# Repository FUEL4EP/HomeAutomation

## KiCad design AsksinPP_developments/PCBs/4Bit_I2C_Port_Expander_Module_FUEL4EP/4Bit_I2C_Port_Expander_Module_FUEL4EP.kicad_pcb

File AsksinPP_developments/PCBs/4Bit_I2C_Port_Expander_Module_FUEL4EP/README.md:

# 4Bit_I2C_Port_Expander_Module_FUEL4EP  

## I2C 4 Port Expander Aufsteckplatine für DIY AsksinPP-Projekte

- basierend auf [PCA9536](https://www.mouser.de/datasheet/2/302/PCA9536-3139488.pdf)

- passend zu
	* [HB-UNI-SEN-BATT_ATMega1284P_E07-868MS10_FUEL4EP](https://github.com/FUEL4EP/HomeAutomation/tree/master/AsksinPP_developments/PCBs/HB-UNI-SEN-BATT_ATMega1284P_E07-868MS10_FUEL4EP)
	* [HB-UNI-SEN-BATT_ATMega1284P_E07-868MS10_FRAM_FUEL4EP](https://github.com/FUEL4EP/HomeAutomation/tree/master/AsksinPP_developments/PCBs/HB-UNI-SEN-BATT_ATMega1284P_E07-868MS10_FRAM_FUEL4EP)
	* [HB-UNI-SEN-BATT_FUEL4EP](https://github.com/FUEL4EP/HomeAutomation/tree/master/AsksinPP_developments/PCBs/HB-UNI-SEN-BATT_FUEL4EP)
	* [HB-UNI-SEN-BATT_ATMega1284P_E07-868MS10_FUEL4EP](https://github.com/FUEL4EP/HomeAutomation/tree/master/AsksinPP_developments/PCBs/HB-UNI-SEN-BATT_ATMega1284P_E07-868MS10_FUEL4EP)
	* Befestigung mit 2 Stiftleisten J1 und J2
	
- 4 zusätzliche PCA9536-IO-Ports, die I2C-steuerbar sind
- 4 zusätzliche 2N7000-Open-Collector-Ausgänge mit Pull-Up Widerständen

- Infos zu AsksinPP sind [hier](https://asksinpp.de) und [hier](https://asksinpp.de/Grundlagen/01_hardware.html#verdrahtung) zu finden

## Platinenmaße

- Breite: 30,48 mm
- Weite: 17 mm
- Platinendicke 1,2 mm (bei der Bestellung bei JLCPCB auswählen)

## Stromlaufplan

- ist [hier](./Schematics/4Bit_I2C_Port_Expander_Module_FUEL4EP.pdf)

## Status

- diese Platine wurde in der Version 1.1 bei JLCPCB gefertigt und ist erfolgreich validiert.
- zum Test wurde der Sketch PCA9536/examples/PCA9536_Test.ino verwendet.

## Rückmeldungen

- und Verbesserungsvorschläge sind willkommen.

## Daten für die Bestellung bei JLCPCB

- die Daten für die Bestellung liegen im Verzeichnis [./jlcpcb/production_files/](./jlcpcb/production_files/)
- Gerber-Daten als Zip-Datei
- BOM- und CPL-Daten als CSV-Datei

## lokale Installation des Github Releases auf Deinem Computer

- gehe bitte in Dein Zielinstallationsverzeichnis, wo Du mit der 4Bit_I2C_Port_Expander_Module_FUEL4EP Platine mit KiCAD arbeiten möchtest

  - gebe dort 'git clone https://github.com/FUEL4EP/HomeAutomation.git' ein
	  + damit lädst Du mein [Sammelrepository](https://github.com/FUEL4EP/HomeAutomation) für alle meine auf Github freigegebenen HomeBrew Entwicklungen herunter.
  - dann findest Du ein neues Verzeichnis 'HomeAutomation' auf Deinem Rechner, das alle meine auf Github freigebenen Entwicklungen enthält, siehe [README.md](https://github.com/FUEL4EP/HomeAutomation/blob/master/README.md)
  	+ mache bitte regelmäßig ein Update mit 'git pull'
 -	die Platine 4Bit_I2C_Port_Expander_Module_FUEL4EP findest Du unter './HomeAutomation/tree/master/AsksinPP_developments/PCBs/4Bit_I2C_Port_Expander_Module_FUEL4EP'
 
- alternativ kann vom Github [Sammelrepository](https://github.com/FUEL4EP/HomeAutomation) die ZIP-Datei HomeAutomation-master.zip heruntergeladen und auf dem lokalen Rechner ausgepackt werden. Bitte dann regelmäßig auf Github nach Updates schauen.

## Versionsverlauf

-   V1.0 03. Sep 2023: Initiale Veröffentlichung auf Github
-	V1.1 16. Dez 2023: Wechsel von 2N7000 auf 2N2007K wegen SMD Gehäuse
-	V1.2 29. Sep 2024: Migration auf KiCAD8
- KiCad Schaltplan-Editor Version: 8.0.5-8.0.5-0~ubuntu22.04.1, release build
 unter Kubuntu22.04.1
- KiCad Leiterplatteneditor Version: 8.0.5-8.0.5-0~ubuntu22.04.1, release build
 unter Kubuntu22.04.1
- PCB Version 1.2
- Schematics  1.2

## Disclaimer

-   die Nutzung der hier veröffentlichten Inhalte erfolgt vollständig auf eigenes Risiko und ohne jede Gewähr.

## Lizenz 

**Creative Commons BY-NC-SA**<br>
Give Credit, NonCommercial, ShareAlike

<br />This work is licensed under a <a rel="license" href="http://creativecommons.org/licenses/by-nc-sa/4.0/">Creative Commons Attribution-NonCommercial-ShareAlike 4.0 International License</a>.

-EOF

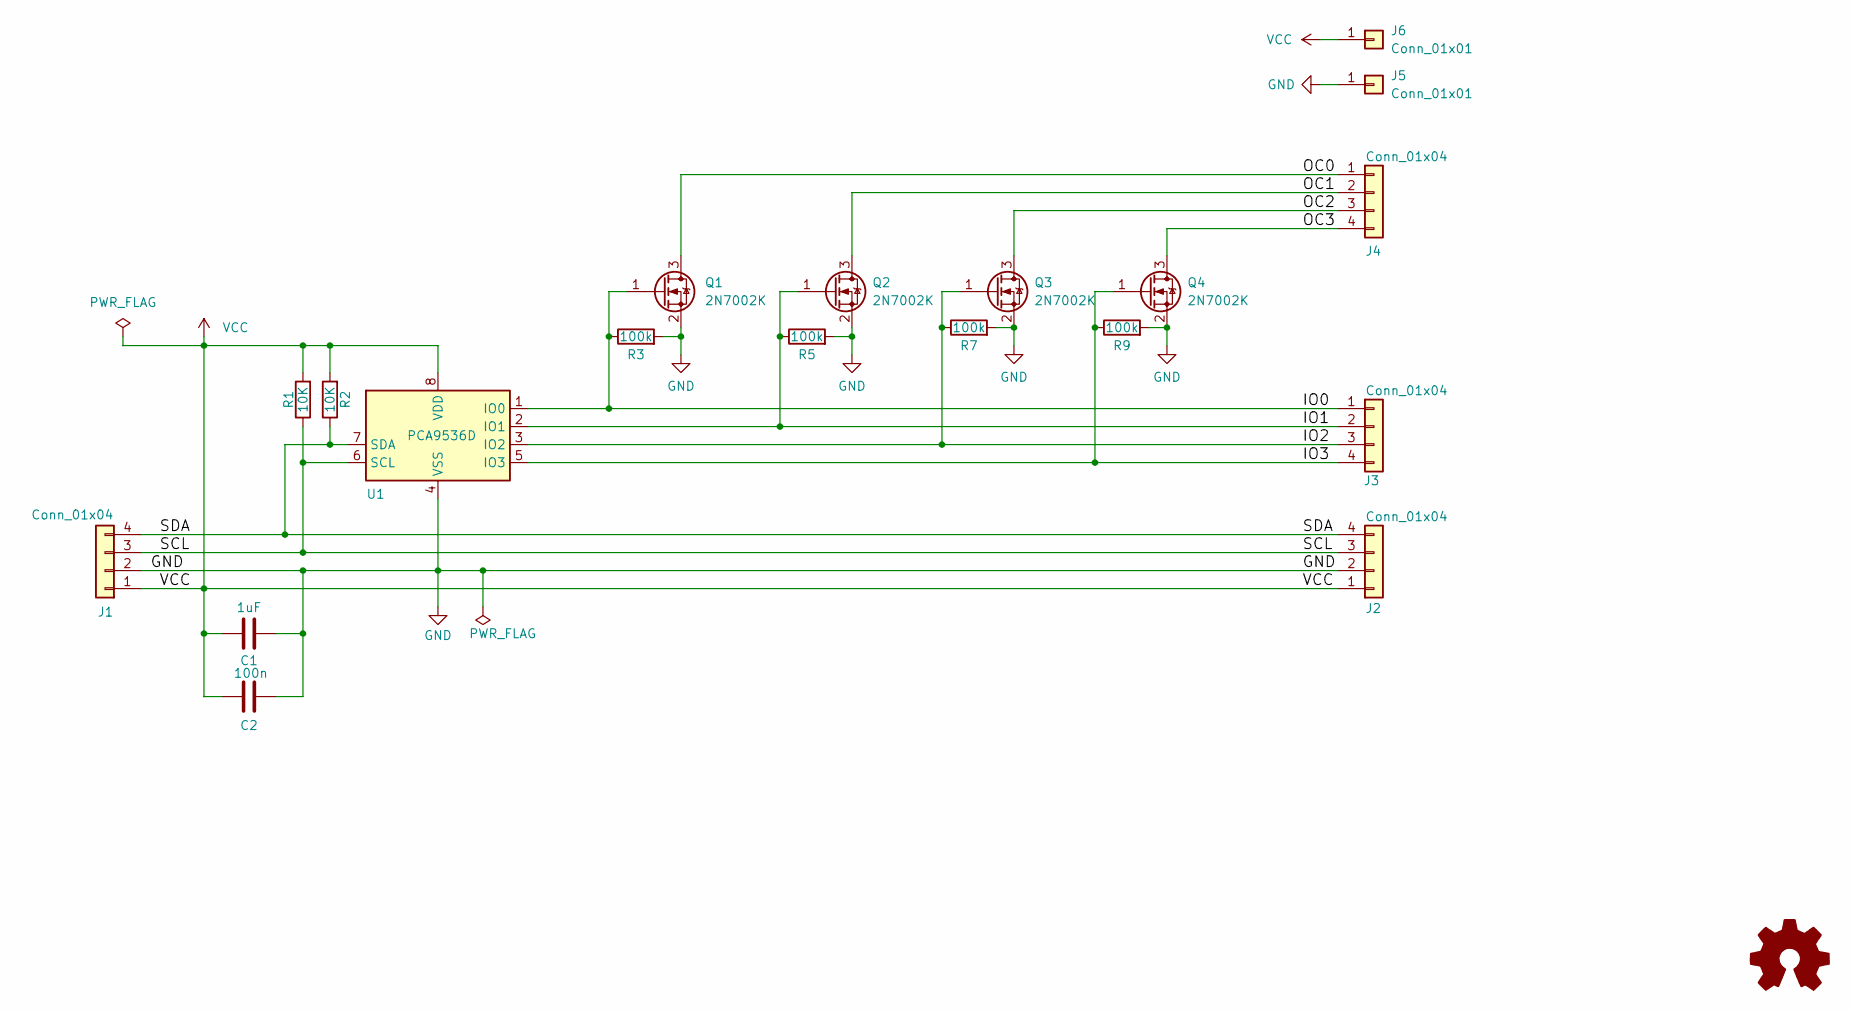
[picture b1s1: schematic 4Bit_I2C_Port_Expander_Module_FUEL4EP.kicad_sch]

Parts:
C1: 1uF; C_0603_1608Metric; LCSC C15849
C2: 100n; C_0402_1005Metric; LCSC C1525
J1, J2, J3, J4: Conn_01x04; PinHeader_1x04_P2.54mm_Vertical
J5, J6: Conn_01x01; TestPoint_THTPad_D1.0mm_Drill0.5mm
LOGO1: Logo_Open_Hardware_Small; CC-BY-ND-SA
Q1, Q2, Q3, Q4: 2N7002K; SOT-23; LCSC C114458
R1, R2: 10K; R_0402_1005Metric; LCSC C25744
R3, R5, R7, R9: 100k; R_0402_1005Metric; LCSC C25741
U1: PCA9536D; SOIC-8_3.9x4.9mm_P1.27mm; LCSC C129522

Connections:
/IO0: J3.1, Q1.1 (G), R3.1, U1.1 (IO0)
/IO1: J3.2, Q2.1 (G), R5.1, U1.2 (IO1)
/IO2: J3.3, Q3.1 (G), R7.1, U1.3 (IO2)
/IO3: J3.4, Q4.1 (G), R9.1, U1.5 (IO3)
/OC0: J4.1, Q1.3 (D)
/OC1: J4.2, Q2.3 (D)
/OC2: J4.3, Q3.3 (D)
/OC3: J4.4, Q4.3 (D)
/SCL: J1.3, J2.3, R1.1, U1.6 (SCL)
/SDA: J1.4, J2.4, R2.1, U1.7 (SDA)
GND: C1.2, C2.2, J1.2, J2.2, J5.1, Q1.2 (S), Q2.2 (S), Q3.2 (S), Q4.2 (S), R3.2, R5.2, R7.2, R9.2, U1.4 (VSS)
VCC: C1.1, C2.1, J1.1, J2.1, J6.1, R1.2, R2.2, U1.8 (VDD)

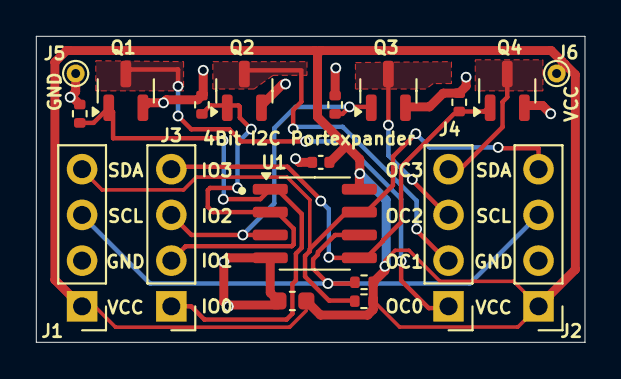
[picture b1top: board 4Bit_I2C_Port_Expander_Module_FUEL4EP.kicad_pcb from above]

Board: 2 copper layers, 30.5 x 17.0 mm, 20 parts (1 on the bottom side), 12 nets.

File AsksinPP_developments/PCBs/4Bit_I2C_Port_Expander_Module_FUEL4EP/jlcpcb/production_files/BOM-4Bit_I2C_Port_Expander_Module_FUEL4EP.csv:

Comment,Designator,Footprint,LCSC
2N7002K,"Q1,Q2,Q3,Q4",SOT-23,C114458
PCA9536D,U1,SOIC-8_3.9x4.9mm_P1.27mm,C129522
100n,C2,C_0402_1005Metric,C1525
1uF,C1,C_0603_1608Metric,C15849
100k,"R3,R5,R7,R9",R_0402_1005Metric,C25741
10K,"R1,R2",R_0402_1005Metric,C25744

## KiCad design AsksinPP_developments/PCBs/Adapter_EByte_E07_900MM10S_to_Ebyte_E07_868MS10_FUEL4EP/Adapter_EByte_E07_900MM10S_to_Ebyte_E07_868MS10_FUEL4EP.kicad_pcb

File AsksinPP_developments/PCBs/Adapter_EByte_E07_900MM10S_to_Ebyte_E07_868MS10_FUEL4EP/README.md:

# Adapter_EByte_E07_900MM10S_to_Ebyte_E07_868MS10_FUEL4EP  

## Ersatz für das eByte E07 868MS10 Modul 

- da das eByte E07 868MS10 Modul nicht mehr oder nur sehr schwer käuflich ist, wurde dieser Adapter als Ersatz entworfen. Es wird ein verfügbares EByte E07 900MM10S Funkmodul verbaut.

## Adapter für 868.3 MHz Funkmodul Ebyte E07 900MM10S auf Ebyte E07 868MS10

- Infos zu AsksinPP sind [hier](https://asksinpp.de) und [hier](https://asksinpp.de/Grundlagen/01_hardware.html#verdrahtung) zu finden

## Platinenmaße

- Breite: 19 mm
- Weite: 13 mm

## Stromlaufplan

- ist [hier](./Schematics/Adapter_EByte_E07_900MM10S_to_Ebyte_E07_868MS10_FUEL4EP.pdf)

## Status

- die Platine V1.1 wurde bei JLCPCB gefertigt und bestückt.
- der Frequenztest wurde am 25. Sep 2024 mit einem PCB HB-UNI-SEN-BATT_ATMega1284P_E07-868MS10_FUEL4EP erfolgreich durchgeführt.
- die Protokolldatei des Frequenztests ist [hier](./Log_files_as_reference/FreqTest_1284P_serial_monitor.log)
- Bilder der gefertigten Prototypen:

## Rückmeldungen

- sind willkommen.

## Daten für die Bestellung bei JLCPCB

- die Daten für die Bestellung liegen im Verzeichnis [./jlcpcb/production_files/](./jlcpcb/production_files/)
- Gerber-Daten als Zip-Datei
- BOM- und CPL-Daten als CSV-Datei

## Hinweis für Bestückung bei JLCPCB

- bei der Bestellung bitte angeben '[specify a location](https://jlcpcb.com/help/article/50-How-to-remove-order-number-from-your-PCB)'

- der  Dummy-Text 'JLCJLCJLCJLC' ist auf der Rückseite der Platine

- Bestückung des Funkmoduls Ebyte E07 900MM10S geht bei JLCPCB nur als teures Standard-PCBA. Handlöten ist eine günstigere Alternative.

## Hinweis für Bestückung von Hand

- die Ferritperle FB1 (0603) kann entweder mit
	+ Murata EMI Suppression Filter SMD0603 BLM18 470 Ohm, erhältlich z.B.  bei Reichelt als Bestellnummer [BLM18AG 471](https://www.reichelt.de/de/de/shop/produkt/emi_suppression_filter_smd0603_blm18_470_ohm-89677)
- oder bei geringeren Anforderungen an Störunterdrückung mit Lötzinn überbrückt werden

## Montage

- die Platine wird mit einer Stiftleiste RM 1.27mm 1x8 Pin auf die Basisplatine gelötet

## lokale Installation des Github Releases auf Deinem Computer

- gehe bitte in Dein Zielinstallationsverzeichnis, wo Du mit der Adapter_EByte_E07_900MM10S_to_Ebyte_E07_868MS10_FUEL4EP Platine mit KiCAD arbeiten möchtest

  - gebe dort 'git clone https://github.com/FUEL4EP/HomeAutomation.git' ein
	  + damit lädst Du mein [Sammelrepository](https://github.com/FUEL4EP/HomeAutomation) für alle meine auf Github freigegebenen HomeBrew Entwicklungen herunter.
  - dann findest Du ein neues Verzeichnis 'HomeAutomation' auf Deinem Rechner, das alle meine auf Github freigebenen Entwicklungen enthält, siehe [README.md](https://github.com/FUEL4EP/HomeAutomation/blob/master/README.md)
  	+ mache bitte regelmäßig ein Update mit 'git pull'
 -	die Platine Adapter_EByte_E07_900MM10S_to_Ebyte_E07_868MS10_FUEL4EP findest Du unter './HomeAutomation/tree/master/AsksinPP_developments/PCBs/Adapter_EByte_E07_900MM10S_to_Ebyte_E07_868MS10_FUEL4EP'
 
- alternativ kann vom Github [Sammelrepository](https://github.com/FUEL4EP/HomeAutomation) die ZIP-Datei HomeAutomation-master.zip heruntergeladen und auf dem lokalen Rechner ausgepackt werden. Bitte dann regelmäßig auf Github nach Updates schauen.

## Versionsverlauf

-   V1.0 24. Jun 2024: Initiale Version
-   V1.1 23. Sep 2024: Migration auf KiCAD 8; zusätzliche Vias
- KiCad Schaltplan-Editor Version: 8.0.5-8.0.5-0~ubuntu22.04.1 unter Kubuntu22.04.1
- KiCad Leiterplatteneditor Version: 8.0.5-8.0.5-0~ubuntu22.04.1 unter Kubuntu22.04.1
- PCB Version 1.1
- Schematics  1.1

## Disclaimer

-   die Nutzung der hier veröffentlichten Inhalte erfolgt vollständig auf eigenes Risiko und ohne jede Gewähr.
-  der Nutzer dieser Platine ist selbst dafür verantwortlich, dass die relevanten Richtlinien für Funkanlagen, z.B. in der EU die Funkanlagenrichtlinie (2014/53/EU, auch bekannt als RED), eingehalten wird.

## Lizenz 

**Creative Commons BY-NC-SA**<br>
Give Credit, NonCommercial, ShareAlike

<br />This work is licensed under a <a rel="license" href="http://creativecommons.org/licenses/by-nc-sa/4.0/">Creative Commons Attribution-NonCommercial-ShareAlike 4.0 International License</a>.

-EOF

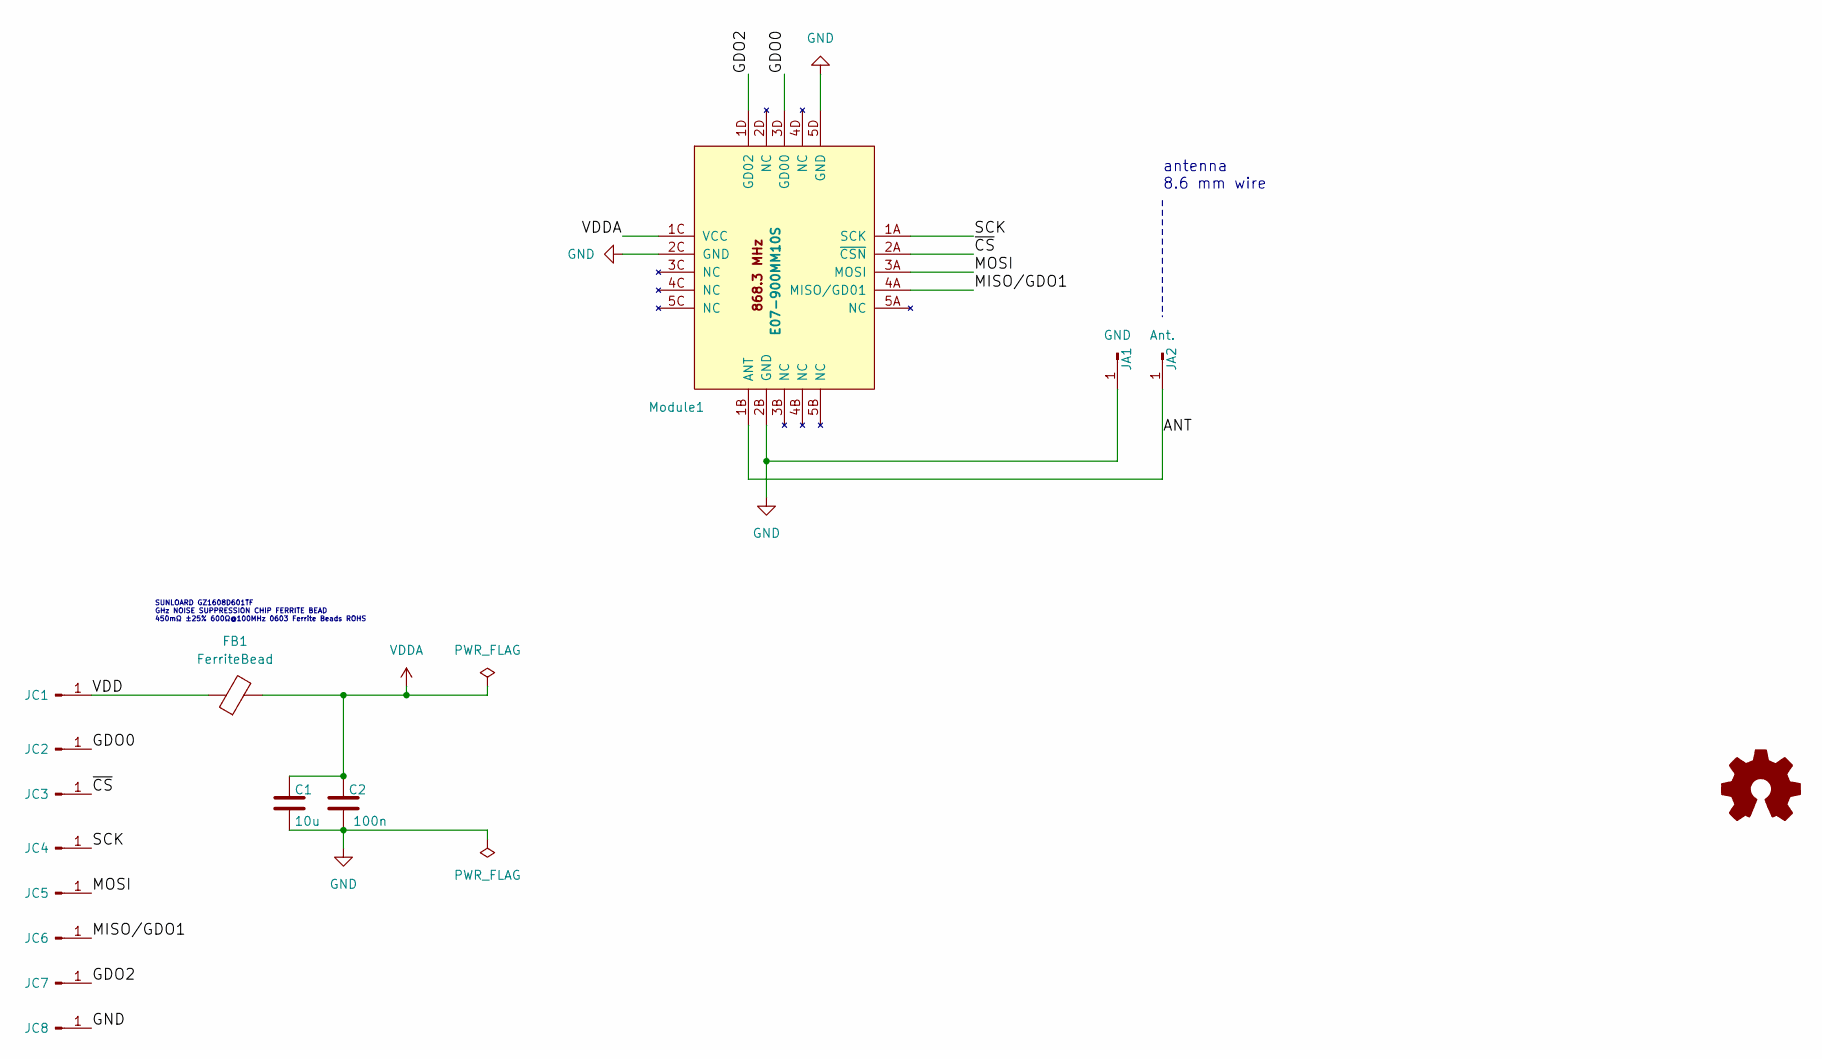
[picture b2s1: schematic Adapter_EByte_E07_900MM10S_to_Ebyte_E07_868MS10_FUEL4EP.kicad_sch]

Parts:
C1: 10u; C_0603_1608Metric; LCSC C19702
C2: 100n; C_0603_1608Metric; LCSC C14663
FB1: FerriteBead; L_0603_1608Metric; LCSC C1002
JA1: GND; edge_hole_Pitch2.28mm_Drill0.8mm
JA2: Ant.; edge_hole_Pitch2.28mm_Drill0.8mm
JC1: Conn_01x01_Pin; edge_hole_Pitch1.27mm_Drill0.75mm
JC2, JC3, JC4, JC5, JC6, JC7, JC8: Conn_01x01_Pin; edge_hole_Pitch1.27mm_Drill0.75mm_rounded
LOGO1: Logo_Open_Hardware_Small; CC-BY-ND-SA_bottom
Module1: E07-900MM10S; eByte_E07-900MM10S; LCSC C5844212

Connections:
/ANT: JA2.1, Module1.1B (ANT)
/GDO0: JC2.1, Module1.3D (GD00)
/GDO2: JC7.1, Module1.1D (GD02)
/MISO/GDO1: JC6.1, Module1.4A (MISO/GD01)
/MOSI: JC5.1, Module1.3A (MOSI)
/SCK: JC4.1, Module1.1A (SCK)
/VDD: FB1.1, JC1.1
/~CS: JC3.1, Module1.2A (~CSN)
GND: C1.2, C2.2, JA1.1, JC8.1, Module1.2B (GND), Module1.2C (GND), Module1.5D (GND)
VDDA: C1.1, C2.1, FB1.2, Module1.1C (VCC)

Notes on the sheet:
SUNLOARD GZ1608D601TF GHz NOISE SUPPRESSION CHIP FERRITE BEAD 450mΩ ±25% 600Ω@100MHz 0603 Ferrite Beads ROHS
antenna 8.6 mm wire

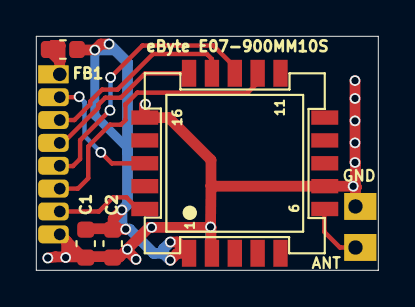
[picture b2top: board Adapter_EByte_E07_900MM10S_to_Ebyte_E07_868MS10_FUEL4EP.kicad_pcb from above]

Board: 2 copper layers, 19.0 x 13.0 mm, 15 parts (0 on the bottom side), 10 nets.

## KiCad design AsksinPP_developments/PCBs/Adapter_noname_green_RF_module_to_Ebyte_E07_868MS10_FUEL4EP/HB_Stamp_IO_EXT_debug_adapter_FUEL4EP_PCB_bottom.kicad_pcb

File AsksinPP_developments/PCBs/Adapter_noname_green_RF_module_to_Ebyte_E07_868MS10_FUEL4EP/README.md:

# Adapter_noname_green_RF_module_to_Ebyte_E07_868MS10_FUEL4EP  

## Ersatz für NoName grüne 868,3 MHz Modul

- da das NoName grüne 868,3 MHz Modul häufig eine schlechte Qualität hat, wurde dieser Adapter als Ersatz entworfen. Es wird ein verfügbares, qualitativ hochwertiges EByte E07 900MM10S Funkmodul mit Abschirmkappe verbaut.

## Adapter für 868.3 MHz Funkmodul Ebyte E07 900MM10S auf NoName grüne 868,3 MHz Modul

- Infos zu AsksinPP sind [hier](https://asksinpp.de) und [hier](https://asksinpp.de/Grundlagen/01_hardware.html#verdrahtung) zu finden

## Platinenmaße

- Breite: 19,2 mm
- Weite: 17 mm

## Stromlaufplan

- ist [hier](./Schematics/Adapter_noname_green_RF_module_to_Ebyte_E07_868MS10_FUEL4EP.pdf)

## Status

- die Platine V1.0 wurde bei JLCPCB gefertigt und werden von Hand bestückt werden
- die Platine ist aber noch nicht validiert
- Bilder der gefertigten Prototypen:
- 

## Rückmeldungen

- sind willkommen.

## Daten für die Bestellung bei JLCPCB

- die Daten für die Bestellung liegen im Verzeichnis [./jlcpcb/production_files/](./jlcpcb/production_files/)
- Gerber-Daten als Zip-Datei
- BOM- und CPL-Daten als CSV-Datei

## Hinweis für Bestückung bei JLCPCB

- bei der Bestellung bitte angeben '[specify a location](https://jlcpcb.com/help/article/50-How-to-remove-order-number-from-your-PCB)'

- der  Dummy-Text 'JLCJLCJLCJLC' ist auf der Rückseite der Platine

- Bestückung des Funkmoduls Ebyte E07 900MM10S geht bei JLCPCB nur als teures Standard-PCBA. Daher löte ich das Funkmodul immer von Hand auf.

## lokale Installation des Github Releases auf Deinem Computer

- gehe bitte in Dein Zielinstallationsverzeichnis, wo Du mit der Adapter_noname_green_RF_module_to_Ebyte_E07_868MS10_FUEL4EP Platine mit KiCAD arbeiten möchtest

  - gebe dort 'git clone https://github.com/FUEL4EP/HomeAutomation.git' ein
	  + damit lädst Du mein [Sammelrepository](https://github.com/FUEL4EP/HomeAutomation) für alle meine auf Github freigegebenen HomeBrew Entwicklungen herunter.
  - dann findest Du ein neues Verzeichnis 'HomeAutomation' auf Deinem Rechner, das alle meine auf Github freigebenen Entwicklungen enthält, siehe [README.md](https://github.com/FUEL4EP/HomeAutomation/blob/master/README.md)
  	+ mache bitte regelmäßig ein Update mit 'git pull'
 -	die Platine Adapter_noname_green_RF_module_to_Ebyte_E07_868MS10_FUEL4EP findest Du unter './HomeAutomation/tree/master/AsksinPP_developments/PCBs/Adapter_noname_green_RF_module_to_Ebyte_E07_868MS10_FUEL4EP'
 
- alternativ kann vom Github [Sammelrepository](https://github.com/FUEL4EP/HomeAutomation) die ZIP-Datei HomeAutomation-master.zip heruntergeladen und auf dem lokalen Rechner ausgepackt werden. Bitte dann regelmäßig auf Github nach Updates schauen.

## Versionsverlauf

-   V1.0 18. Apr 2025: Initiale Version
- KiCad Schaltplan-Editor Version: 8.0.5-8.0.5-0~ubuntu22.04.1 unter Kubuntu22.04.1
- KiCad Leiterplatteneditor Version: 8.0.5-8.0.5-0~ubuntu22.04.1 unter Kubuntu22.04.1
- PCB Version 1.0
- Schematics  1.0

## Disclaimer

-   die Nutzung der hier veröffentlichten Inhalte erfolgt vollständig auf eigenes Risiko und ohne jede Gewähr.
-  der Nutzer dieser Platine ist selbst dafür verantwortlich, dass die relevanten Richtlinien für Funkanlagen, z.B. in der EU die Funkanlagenrichtlinie (2014/53/EU, auch bekannt als RED), eingehalten wird.

## Lizenz 

**Creative Commons BY-NC-SA**<br>
Give Credit, NonCommercial, ShareAlike

<br />This work is licensed under a <a rel="license" href="http://creativecommons.org/licenses/by-nc-sa/4.0/">Creative Commons Attribution-NonCommercial-ShareAlike 4.0 International License</a>.

-EOF

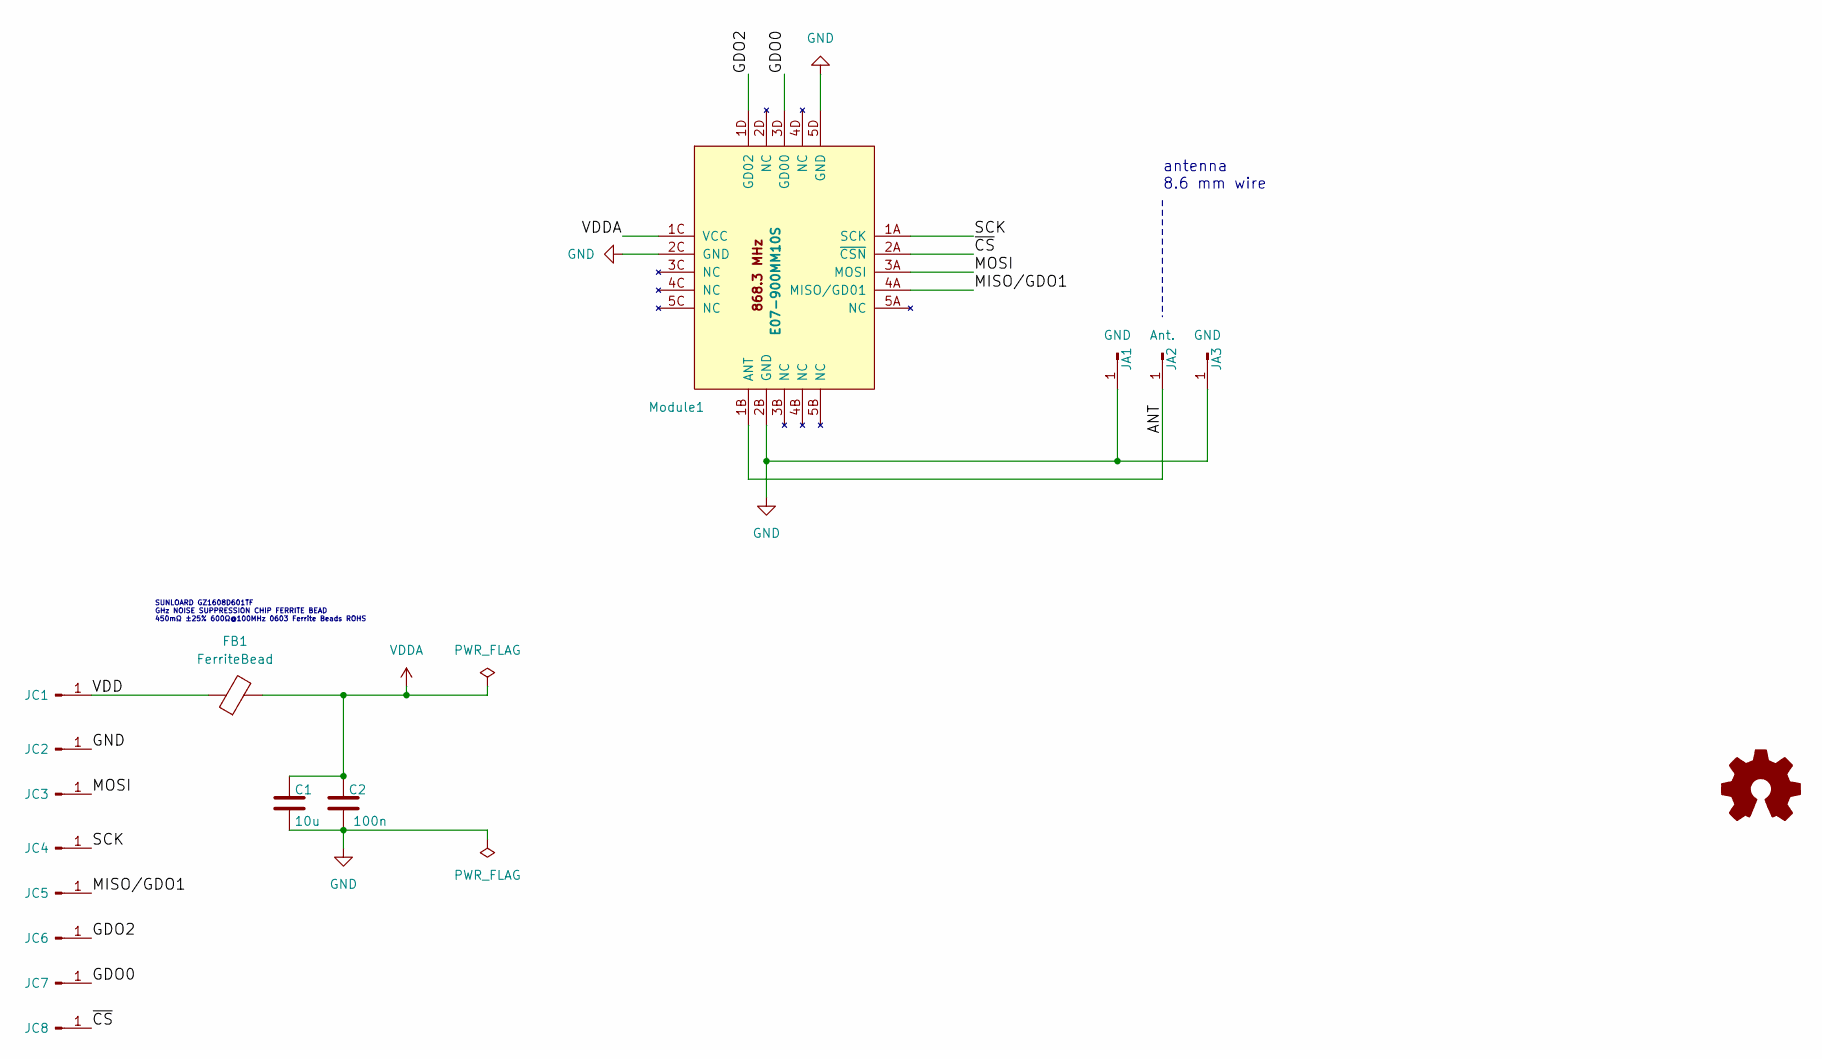
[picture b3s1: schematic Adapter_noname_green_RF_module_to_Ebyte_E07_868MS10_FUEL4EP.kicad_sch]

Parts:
C1: 10u; C_0603_1608Metric; LCSC C19702
C2: 100n; C_0603_1608Metric; LCSC C14663
FB1: FerriteBead; L_0603_1608Metric; LCSC C1002
JA1, JA3: GND; hole_Pitch2.54mm_Drill0.9mm
JA2: Ant.; hole_Pitch2.54mm_Drill0.9mm
JC1: Conn_01x01_Pin; hole_Pitch2.00mm_Drill0.8mm
JC2, JC3, JC4, JC5, JC6, JC7, JC8: Conn_01x01_Pin; hole_Pitch2.00mm_Drill0.8mm_rounded
LOGO1: Logo_Open_Hardware_Small; CC-BY-ND-SA_bottom
Module1: E07-900MM10S; eByte_E07-900MM10S; LCSC C5844212

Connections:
/ANT: JA2.1, Module1.1B (ANT)
/GDO0: JC7.1, Module1.3D (GD00)
/GDO2: JC6.1, Module1.1D (GD02)
/MISO/GDO1: JC5.1, Module1.4A (MISO/GD01)
/MOSI: JC3.1, Module1.3A (MOSI)
/SCK: JC4.1, Module1.1A (SCK)
/VDD: FB1.1, JC1.1
/~CS: JC8.1, Module1.2A (~CSN)
GND: C1.2, C2.2, JA1.1, JA3.1, JC2.1, Module1.2B (GND), Module1.2C (GND), Module1.5D (GND)
VDDA: C1.1, C2.1, FB1.2, Module1.1C (VCC)

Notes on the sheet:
SUNLOARD GZ1608D601TF GHz NOISE SUPPRESSION CHIP FERRITE BEAD 450mΩ ±25% 600Ω@100MHz 0603 Ferrite Beads ROHS
antenna 8.6 mm wire

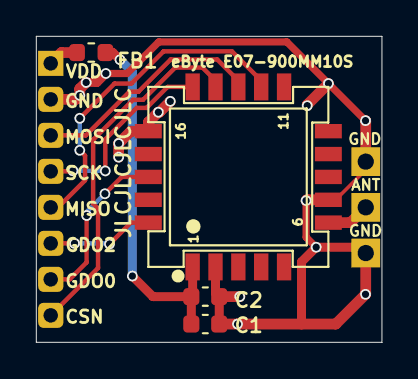
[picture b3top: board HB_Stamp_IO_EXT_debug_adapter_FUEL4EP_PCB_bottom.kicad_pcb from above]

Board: 2 copper layers, 19.2 x 17.0 mm, 16 parts (0 on the bottom side), 10 nets.

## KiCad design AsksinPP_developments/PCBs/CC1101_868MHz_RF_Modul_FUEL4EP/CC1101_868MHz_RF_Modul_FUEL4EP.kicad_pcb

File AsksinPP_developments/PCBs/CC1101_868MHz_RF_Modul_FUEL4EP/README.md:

# CC1101_868MHz_RF_Modul_FUEL4EP  

## 868,3 MHz Funkmodul für AsksinPP DIY Projekte

- Infos zu AsksinPP sind [hier](https://asksinpp.de) und [hier](https://asksinpp.de/Grundlagen/01_hardware.html#verdrahtung) zu finden

## Platinenmaße

- Breite: 19 mm
- Weite: 13 mm
- Platinendicke **1,2 mm** (bei der Bestellung bei JLCPCB auswählen)

## Stromlaufplan

- ist [hier](./Schematics/CC1101_868MHz_RF_Modul_FUEL4EP.pdf)

## Danksagung

- diese Platine ist abgeleitet von [CC1101_Module](https://github.com/jp112sdl/CC1101_Module)
- mein besonderer Dank geht an [Jérôme](https://github.com/jp112sdl) und [papa](https://github.com/pa-pa) für ihre Vorarbeit und alle, die im [Forum](https://homematic-forum.de/forum/viewtopic.php?f=76&t=79770&sid=9a4abe34301506f133d423b0580074a5) zu dieser Platine beigetragen haben.
-
## Status

- diese Platine wurde in der Version V1.6 bei JLCPCB gefertigt und wurde erfolgreich validiert
- die Validierungsergebnisse sind [hier](./Prototype_Validation) zu finden

## Ersatz für das eByte E07 868MS10 Modul

- da das eByte E07 868MS10 Modul nicht mehr oder nur sehr schwer käuflich ist, wurde dieses Modul als pinkompatibler Ersatz entworfen

## Rückmeldungen

- und Verbesserungsvorschläge sind [hier](https://homematic-forum.de/forum/viewtopic.php?f=76&t=79770&sid=9a4abe34301506f133d423b0580074a5) willkommen.

## Daten für die Bestellung bei JLCPCB

- die Daten für die Bestellung liegen im Verzeichnis [./jlcpcb/production_files/](./jlcpcb/production_files/)
- Gerber-Daten als Zip-Datei
- BOM- und CPL-Daten als CSV-Datei
- bei der Bestellung bitte angeben '[specify a location](https://jlcpcb.com/help/article/50-How-to-remove-order-number-from-your-PCB)'

- der  Dummy-Text 'JLCJLCJLCJLC' ist auf der Rückseite der Platine
- C8 und C9 sollen 1% C0G Kondensatoren sein
- **als Platinendicke unbedingt bei der Bestellung angeben: 1,2 mm (bitte nicht ändern)**

## lokale Installation des Github Releases auf Deinem Computer

- gehe bitte in Dein Zielinstallationsverzeichnis, wo Du mit der CC1101_868MHz_RF_Modul_FUEL4EP Platine mit KiCAD arbeiten möchtest

  - gebe dort 'git clone https://github.com/FUEL4EP/HomeAutomation.git' ein
	  + damit lädst Du mein [Sammelrepository](https://github.com/FUEL4EP/HomeAutomation) für alle meine auf Github freigegebenen HomeBrew Entwicklungen herunter.
  - dann findest Du ein neues Verzeichnis 'HomeAutomation' auf Deinem Rechner, das alle meine auf Github freigebenen Entwicklungen enthält, siehe [README.md](https://github.com/FUEL4EP/HomeAutomation/blob/master/README.md)
  	+ mache bitte regelmäßig ein Update mit 'git pull'
 -	die Platine CC1101_868MHz_RF_Modul_FUEL4EP findest Du unter './HomeAutomation/tree/master/AsksinPP_developments/PCBs/CC1101_868MHz_RF_Modul_FUEL4EP'
 
- alternativ kann vom Github [Sammelrepository](https://github.com/FUEL4EP/HomeAutomation) die ZIP-Datei HomeAutomation-master.zip heruntergeladen und auf dem lokalen Rechner ausgepackt werden. Bitte dann regelmäßig auf Github nach Updates schauen.

## Versionsverlauf

-   V1.3 01. Sep 2023: Anpassung der Silkscreen-Texte and JLCPCB-Regeln
-   V1.4 12. Sep 2023: Verbesserung der GND-Durchkontaktierungen
-   V1.5 21. Sep 2023: Verbesserung der Entkopplungskondensatoren mit kürzeren GND-Stromschleifen zur Impedanzverringerung
-   V1.6 29. Sep 2023: Reduktion der parasitischen Kapazitäten des Oszillators; 1% CoG Kapazitäten für C8 und C9
-   S V1.4 30. Sep 2024 Migration auf KiCAD 8
-   L V1.7 30. Sep 2024 Migration auf KiCAD 8
- KiCad Schaltplan-Editor Version:  8.0.5-8.0.5-0~ubuntu22.04.1, release build unter Kubuntu22.04.1
- KiCad Leiterplatteneditor Version:  8.0.5-8.0.5-0~ubuntu22.04.1, release build unter Kubuntu22.04.1
- PCB Version 1.7
- Schematics  1.4

## Sammelbestellung

- wer Interesse an einer gemeinsamen Bestellung von Platinen und/oder Gehäusen bei JLCPCB hat, fragt bitte per per PN bei bei [FUEL4EP](https://homematic-forum.de/forum/ucp.php?i=pm&mode=compose&u=20685) an.
- wenn genügend Interesse (>= 20 bestückte Platinen und/oder 3D gedruckten Gehäusen) zustande kommt, biete ich an, Platinen  und Gehäuse gegen Vorkasse per PayPal zum Selbstkostenpreis + Versandkosten + 3 Euro Aufwandspauschale pro Versand bei JLCPCB zu bestellen und dann weiterzuverkaufen. Vor einer Bestellung wird ein Angebot bei JLCPCB eingeholt und an die Interessenten zur Zustimmung verteilt.

## alternative günstigere Lösung mit Adapterplatine

- zur Zeit ist eine Adapterplatine [Adapter_EByte_E07_900MM10S_to_Ebyte_E07_868MS10_FUEL4EP](https://github.com/FUEL4EP/HomeAutomation/tree/master/AsksinPP_developments/PCBs/Adapter_EByte_E07_900MM10S_to_Ebyte_E07_868MS10_FUEL4EP) mit aufgelötetetem Modul eByte E07 900MM10S Funkmodul günstiger als das Modul CC1101_868MHz_RF_Modul_FUEL4EP

## Disclaimer

-   die Nutzung der hier veröffentlichten Inhalte erfolgt vollständig auf eigenes Risiko und ohne jede Gewähr.
-	der Nutzer dieser Platine ist selbst dafür verantwortlich, dass die relevanten Richtlinien für Funkanlagen, z.B. in der EU die Funkanlagenrichtlinie (2014/53/EU, auch bekannt als RED), eingehalten wird.

## Lizenz 

**Creative Commons BY-NC-SA**<br>
Give Credit, NonCommercial, ShareAlike

<br />This work is licensed under a <a rel="license" href="http://creativecommons.org/licenses/by-nc-sa/4.0/">Creative Commons Attribution-NonCommercial-ShareAlike 4.0 International License</a>.

-EOF

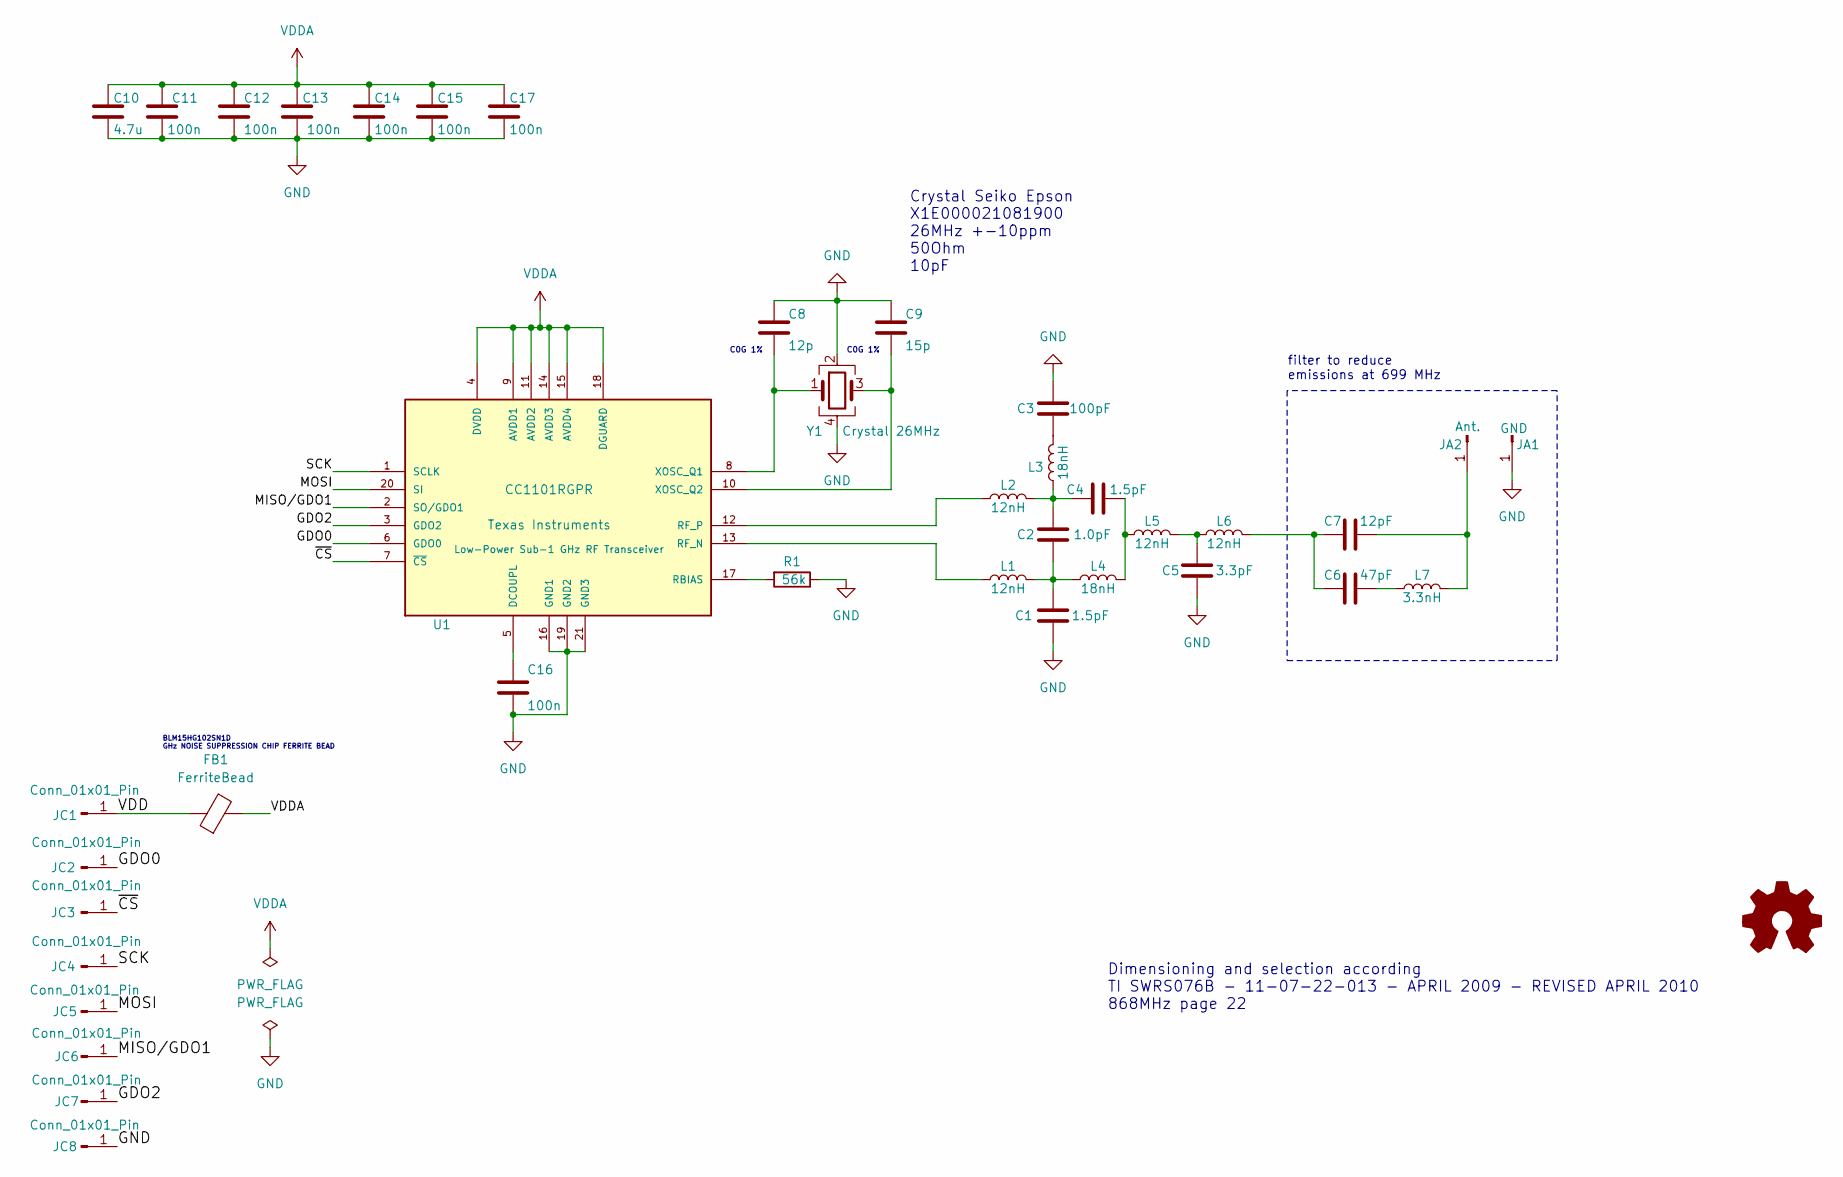
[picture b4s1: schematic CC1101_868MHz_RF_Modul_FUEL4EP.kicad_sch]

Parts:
C1, C4: 1.5pF; C_0402_1005Metric; LCSC C76901
C2: 1.0pF; C_0402_1005Metric; LCSC C710646
C3: 100pF; C_0402_1005Metric; LCSC C1546
C5: 3.3pF; C_0402_1005Metric; LCSC C1565
C6: 47pF; C_0402_1005Metric; LCSC C384800
C7: 12pF; C_0402_1005Metric; LCSC C1547
C8: 12p; C_0402_1005Metric; LCSC C393682
C9: 15p; C_0402_1005Metric; LCSC C441742
C10: 4.7u; C_0402_1005Metric; LCSC C23733
C11, C12, C14, C15, C16, C17: 100n; C_0402_1005Metric; LCSC C1525
C13: 100n; C_0603_1608Metric; LCSC C14663
FB1: FerriteBead; L_0402_1005Metric; LCSC C76889
JA1: GND; edge_hole_Pitch1.27mm_Drill0.75mm
JA2: Ant.; edge_hole_Pitch1.27mm_Drill0.75mm
JC1: Conn_01x01_Pin; edge_hole_Pitch1.27mm_Drill0.75mm
JC2, JC3, JC4, JC5, JC6, JC7, JC8: Conn_01x01_Pin; edge_hole_Pitch1.27mm_Drill0.75mm_rounded
L1, L2, L5, L6: 12nH; L_0402_1005Metric; LCSC C2043991
L3, L4: 18nH; L_0402_1005Metric; LCSC C908004
L7: 3.3nH; L_0402_1005Metric; LCSC C412273
R1: 56k; R_0402_1005Metric; LCSC C25796
U1: CC1101RGPR; Texas_RGP0020H_VQFN-20-1EP_4x4mm_P0.5mm_EP2.4x2.4mm_Thermal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; LCSC C29953
Y1: Crystal 26MHz; Crystal_SMD_3225-4Pin_3.2x2.5mm; LCSC C91747

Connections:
/GDO0: JC2.1, U1.6 (GDO0)
/GDO2: JC7.1, U1.3 (GDO2)
/MISO/GDO1: JC6.1, U1.2 (SO/GDO1)
/MOSI: JC5.1, U1.20 (SI)
/SCK: JC4.1, U1.1 (SCLK)
/VDD: FB1.1, JC1.1
/~CS: JC3.1, U1.7 (~CS)
GND: C1.2, C3.1, C5.1, C8.1, C9.1, C10.2, C11.2, C12.2, C13.2, C14.2, C15.2, C16.2, C17.2, JA1.1, JC8.1, R1.1, U1.16 (GND1), U1.19 (GND2), U1.21 (GND3), Y1.2, Y1.4
unnamed: C1.1, C2.2, L1.2, L4.1
unnamed: C2.1, C4.1, L2.2, L3.1
unnamed: C3.2, L3.2
unnamed: C4.2, L4.2, L5.1
unnamed: C5.2, L5.2, L6.1
unnamed: C6.1, L7.1
unnamed: C6.2, C7.2, L6.2
unnamed: C7.1, JA2.1, L7.2
unnamed: C16.1, U1.5 (DCOUPL)
unnamed: R1.2, U1.17 (RBIAS)
unnamed: L1.1, U1.13 (RF_N)
unnamed: L2.1, U1.12 (RF_P)
unnamed: C8.2, U1.8 (XOSC_Q1), Y1.1
unnamed: C9.2, U1.10 (XOSC_Q2), Y1.3
VDDA: C10.1, C11.1, C12.1, C13.1, C14.1, C15.1, C17.1, FB1.2, U1.4 (DVDD), U1.9 (AVDD1), U1.11 (AVDD2), U1.14 (AVDD3), U1.15 (AVDD4), U1.18 (DGUARD)

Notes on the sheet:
BLM15HG102SN1D GHz NOISE SUPPRESSION CHIP FERRITE BEAD
Dimensioning and selection according TI SWRS076B - 11-07-22-013 - APRIL 2009 - REVISED APRIL 2010 868MHz page 22
filter to reduce emissions at 699 MHz
Crystal Seiko Epson X1E000021081900 26MHz +-10ppm 50Ohm 10pF
C0G 1%

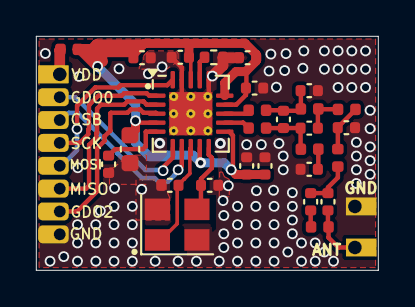
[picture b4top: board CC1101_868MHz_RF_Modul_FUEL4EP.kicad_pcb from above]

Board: 2 copper layers, 19.0 x 13.0 mm, 38 parts (0 on the bottom side), 23 nets.

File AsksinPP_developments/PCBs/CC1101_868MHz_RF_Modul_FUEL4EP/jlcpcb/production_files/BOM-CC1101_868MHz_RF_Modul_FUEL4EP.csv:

Comment,Designator,Footprint,LCSC
100n,C13,C_0603_1608Metric,C14663
100n,"C11,C12,C14,C15,C16,C17",C_0402_1005Metric,C1525
100pF,C3,C_0402_1005Metric,C1546
12pF,C7,C_0402_1005Metric,C1547
3.3pF,C5,C_0402_1005Metric,C1565
12nH,"L1,L2,L5,L6",L_0402_1005Metric,C2043991
4.7u,C10,C_0402_1005Metric,C23733
56k,R1,R_0402_1005Metric,C25796
CC1101RGPR,U1,Texas_RGP0020H_VQFN-20-1EP_4x4mm_P0.5mm_EP2.4x2.4mm_ThermalVias,C29953
47pF,C6,C_0402_1005Metric,C384800
12p,C8,C_0402_1005Metric,C393682
3.3nH,L7,L_0402_1005Metric,C412273
15p,C9,C_0402_1005Metric,C441742
1.0pF,C2,C_0402_1005Metric,C710646
FerriteBead,FB1,L_0402_1005Metric,C76889
1.5pF,"C1,C4",C_0402_1005Metric,C76901
18nH,"L3,L4",L_0402_1005Metric,C908004
Crystal  26MHz,Y1,Crystal_SMD_3225-4Pin_3.2x2.5mm,C91747

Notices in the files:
AsksinPP_developments/PCBs/4Bit_I2C_Port_Expander_Module_FUEL4EP/4Bit_I2C_Port_Expander_Module_FUEL4EP.kicad_sch:
Creative Commons License, non-commercial
AsksinPP_developments/PCBs/4Bit_I2C_Port_Expander_Module_FUEL4EP/README.md:
License: CC BY-NC-SA 4.0
